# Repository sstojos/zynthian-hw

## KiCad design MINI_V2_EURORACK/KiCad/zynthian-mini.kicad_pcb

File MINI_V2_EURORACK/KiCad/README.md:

This repo include design details for building PCB for Zynthian MINI V2 to fit inside the Eurorack case.

PCB is designed usign KiCad software. 

This repository also include PCB that is used as a facia.

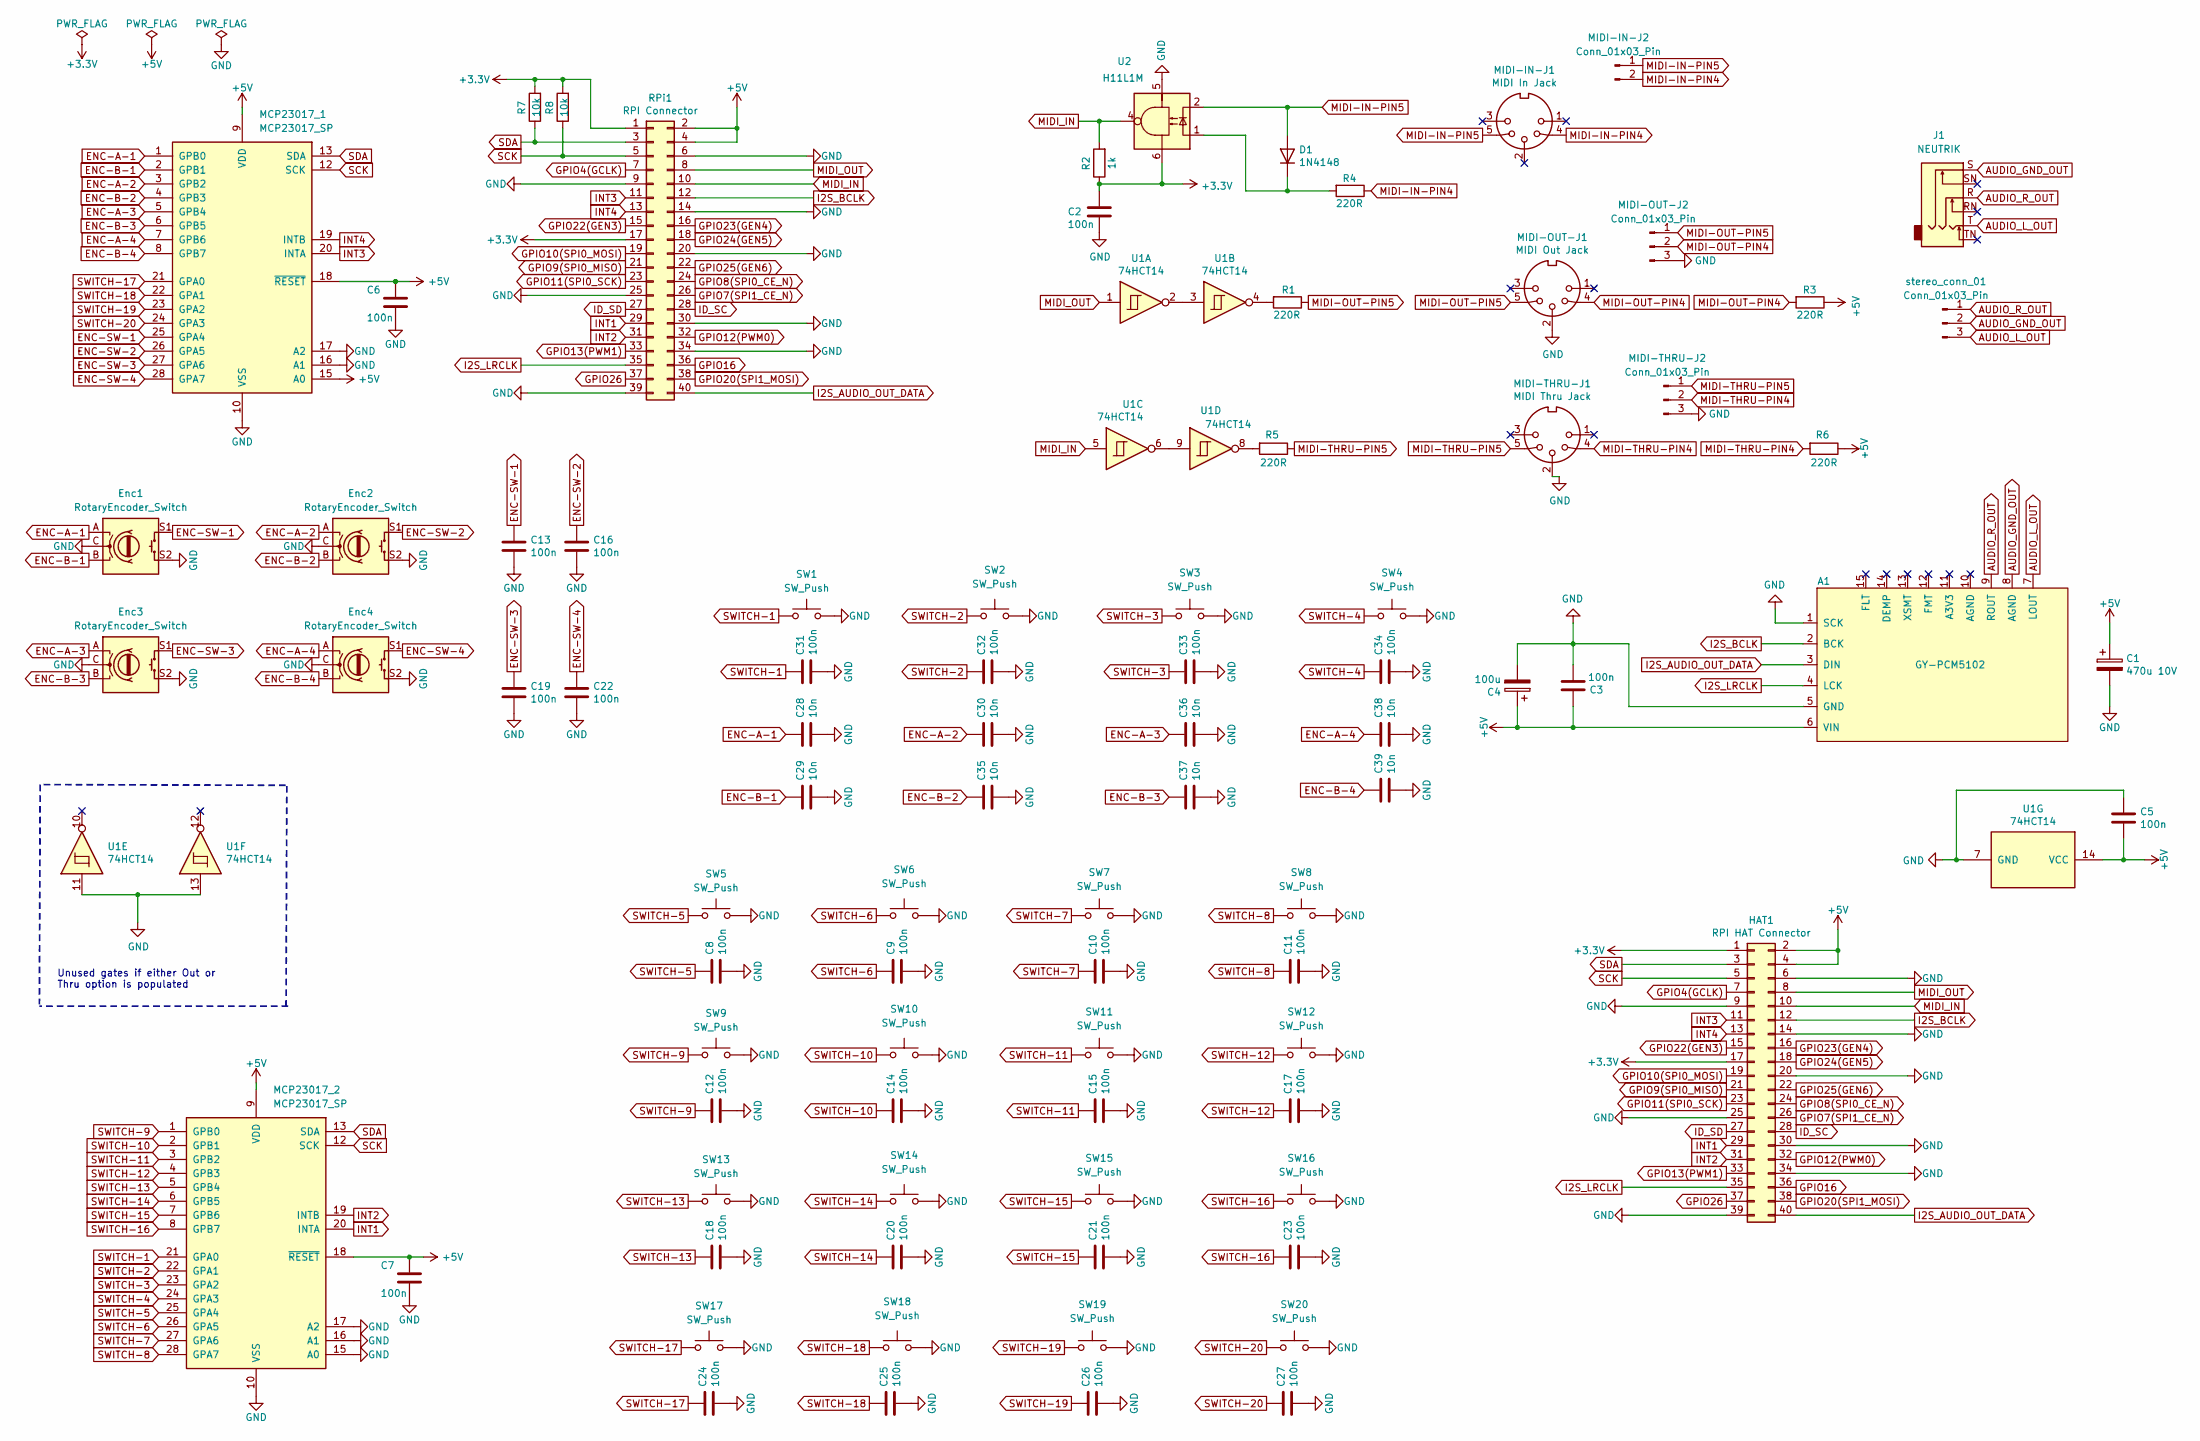
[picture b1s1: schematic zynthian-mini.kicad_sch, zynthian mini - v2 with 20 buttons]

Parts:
A1: GY-PCM5102
C1: 470u 10V; CP_Radial_D8.0mm_P3.50mm
C2, C3, C5, C6, C7: 100n; C_Rect_L7.0mm_W2.0mm_P5.00mm
C4: 100u; CP_Radial_D6.3mm_P2.50mm
C8, C9, C10, C11, C12, C13, C14, C15, C16, C17, C18, C19, C20, C21, C22, C23, C24, C25, C26, C27, C31, C32, C33, C34: 100n; C_Rect_L4.0mm_W2.5mm_P2.50mm
C28, C29, C30, C35, C36, C37, C38, C39: 10n; C_Rect_L4.0mm_W2.5mm_P2.50mm
D1: 1N4148; D_DO-35_SOD27_P7.62mm_Horizontal
Enc1, Enc2, Enc3, Enc4: RotaryEncoder_Switch; RotaryEncoder_Alps_EC12E-Switch_Vertical_H20mm
HAT1: RPI HAT Connector; raspberry pi 4
J1: NEUTRIK; Jack_6.35mm_Neutrik_NMJ6HFD2_Horizontal
MCP23017_1, MCP23017_2: MCP23017_SP; DIP-28_W7.62mm
MIDI-IN-J1: MIDI In Jack; MultiDIN5
MIDI-IN-J2: Conn_01x03_Pin; PinHeader_1x02_P2.54mm_Vertical
MIDI-OUT-J1: MIDI Out Jack; MultiDIN5
MIDI-OUT-J2: Conn_01x03_Pin; PinHeader_1x03_P2.54mm_Vertical
MIDI-THRU-J1: MIDI Thru Jack; MultiDIN5
MIDI-THRU-J2: Conn_01x03_Pin; PinHeader_1x03_P2.54mm_Vertical
R1, R3, R4, R5, R6: 220R; R_Axial_DIN0207_L6.3mm_D2.5mm_P7.62mm_Horizontal
R2: 1k; R_Axial_DIN0207_L6.3mm_D2.5mm_P7.62mm_Horizontal
R7, R8: 10k; R_Axial_DIN0207_L6.3mm_D2.5mm_P7.62mm_Horizontal
RPi1: RPI Connector; raspberry pi 4 HAT
SW1, SW2, SW3, SW4, SW5, SW6, SW7, SW8, SW9, SW10, SW11, SW12, SW13, SW14, SW15, SW16, SW17, SW18, SW19, SW20: SW_Push; push-button-13mm
U1: 74HCT14; DIP-14_W7.62mm
U2: H11L1M; DIP-6_W7.62mm
stereo_conn_01: Conn_01x03_Pin; PinHeader_1x03_P2.54mm_Vertical

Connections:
AUDIO_GND_OUT: A1.8 (AGND), J1.S, stereo_conn_01.2
AUDIO_L_OUT: A1.7 (LOUT), J1.T, stereo_conn_01.3
AUDIO_R_OUT: A1.9 (ROUT), J1.R, stereo_conn_01.1
ENC-A-1: C28.1, Enc1.A, MCP23017_1.1 (GPB0)
ENC-A-2: C30.1, Enc2.A, MCP23017_1.3 (GPB2)
ENC-A-3: C36.1, Enc3.A, MCP23017_1.5 (GPB4)
ENC-A-4: C38.1, Enc4.A, MCP23017_1.7 (GPB6)
ENC-B-1: C29.1, Enc1.B, MCP23017_1.2 (GPB1)
ENC-B-2: C35.1, Enc2.B, MCP23017_1.4 (GPB3)
ENC-B-3: C37.1, Enc3.B, MCP23017_1.6 (GPB5)
ENC-B-4: C39.1, Enc4.B, MCP23017_1.8 (GPB7)
ENC-SW-1: C13.1, Enc1.S1, MCP23017_1.25 (GPA4)
ENC-SW-2: C16.1, Enc2.S1, MCP23017_1.26 (GPA5)
ENC-SW-3: C19.1, Enc3.S1, MCP23017_1.27 (GPA6)
ENC-SW-4: C22.1, Enc4.S1, MCP23017_1.28 (GPA7)
GPIO4(GCLK): HAT1.7, RPi1.7
GPIO7(SPI1_CE_N): HAT1.26, RPi1.26
GPIO8(SPI0_CE_N): HAT1.24, RPi1.24
GPIO9(SPI0_MISO): HAT1.21, RPi1.21
GPIO10(SPI0_MOSI): HAT1.19, RPi1.19
GPIO11(SPI0_SCK): HAT1.23, RPi1.23
GPIO12(PWM0): HAT1.32, RPi1.32
GPIO13(PWM1): HAT1.33, RPi1.33
GPIO16: HAT1.36, RPi1.36
GPIO20(SPI1_MOSI): HAT1.38, RPi1.38
GPIO22(GEN3): HAT1.15, RPi1.15
GPIO23(GEN4): HAT1.16, RPi1.16
GPIO24(GEN5): HAT1.18, RPi1.18
GPIO25(GEN6): HAT1.22, RPi1.22
GPIO26: HAT1.37, RPi1.37
I2S_AUDIO_OUT_DATA: A1.3 (DIN), HAT1.40, RPi1.40
I2S_BCLK: A1.2 (BCK), HAT1.12, RPi1.12
I2S_LRCLK: A1.4 (LCK), HAT1.35, RPi1.35
ID_SC: HAT1.28, RPi1.28
ID_SD: HAT1.27, RPi1.27
INT1: HAT1.29, MCP23017_2.20 (INTA), RPi1.29
INT2: HAT1.31, MCP23017_2.19 (INTB), RPi1.31
INT3: HAT1.11, MCP23017_1.20 (INTA), RPi1.11
INT4: HAT1.13, MCP23017_1.19 (INTB), RPi1.13
MIDI-IN-PIN4: MIDI-IN-J1.4, MIDI-IN-J2.2, R4.1
MIDI-IN-PIN5: D1.2 (A), MIDI-IN-J1.5, MIDI-IN-J2.1, U2.2
MIDI-OUT-PIN4: MIDI-OUT-J1.4, MIDI-OUT-J2.2, R3.2
MIDI-OUT-PIN5: MIDI-OUT-J1.5, MIDI-OUT-J2.1, R1.1
MIDI-THRU-PIN4: MIDI-THRU-J1.4, MIDI-THRU-J2.2, R6.2
MIDI-THRU-PIN5: MIDI-THRU-J1.5, MIDI-THRU-J2.1, R5.1
MIDI_IN: HAT1.10, R2.2, RPi1.10, U1.5, U2.4
MIDI_OUT: HAT1.8, RPi1.8, U1.1
unnamed: D1.1 (K), R4.2, U2.1
unnamed: R1.2, U1.4
unnamed: R5.2, U1.8
unnamed: U1.2, U1.3
unnamed: U1.6, U1.9
SCK: HAT1.5, MCP23017_1.12 (SCK), MCP23017_2.12 (SCK), R8.1, RPi1.5
SDA: HAT1.3, MCP23017_1.13 (SDA), MCP23017_2.13 (SDA), R7.1, RPi1.3
SWITCH-1: C31.1, MCP23017_2.21 (GPA0), SW1.1
SWITCH-2: C32.1, MCP23017_2.22 (GPA1), SW2.1
SWITCH-3: C33.1, MCP23017_2.23 (GPA2), SW3.1
SWITCH-4: C34.1, MCP23017_2.24 (GPA3), SW4.1
SWITCH-5: C8.1, MCP23017_2.25 (GPA4), SW5.1
SWITCH-6: C9.1, MCP23017_2.26 (GPA5), SW6.1
SWITCH-7: C10.1, MCP23017_2.27 (GPA6), SW7.1
SWITCH-8: C11.1, MCP23017_2.28 (GPA7), SW8.1
SWITCH-9: C12.1, MCP23017_2.1 (GPB0), SW9.1
SWITCH-10: C14.1, MCP23017_2.2 (GPB1), SW10.1
SWITCH-11: C15.1, MCP23017_2.3 (GPB2), SW11.1
SWITCH-12: C17.1, MCP23017_2.4 (GPB3), SW12.1
SWITCH-13: C18.1, MCP23017_2.5 (GPB4), SW13.1
SWITCH-14: C20.1, MCP23017_2.6 (GPB5), SW14.1
SWITCH-15: C21.1, MCP23017_2.7 (GPB6), SW15.1
SWITCH-16: C23.1, MCP23017_2.8 (GPB7), SW16.1
SWITCH-17: C24.1, MCP23017_1.21 (GPA0), SW17.1
SWITCH-18: C25.1, MCP23017_1.22 (GPA1), SW18.1
SWITCH-19: C26.1, MCP23017_1.23 (GPA2), SW19.1
SWITCH-20: C27.1, MCP23017_1.24 (GPA3), SW20.1

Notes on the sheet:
Unused gates if either Out or Thru option is populated

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
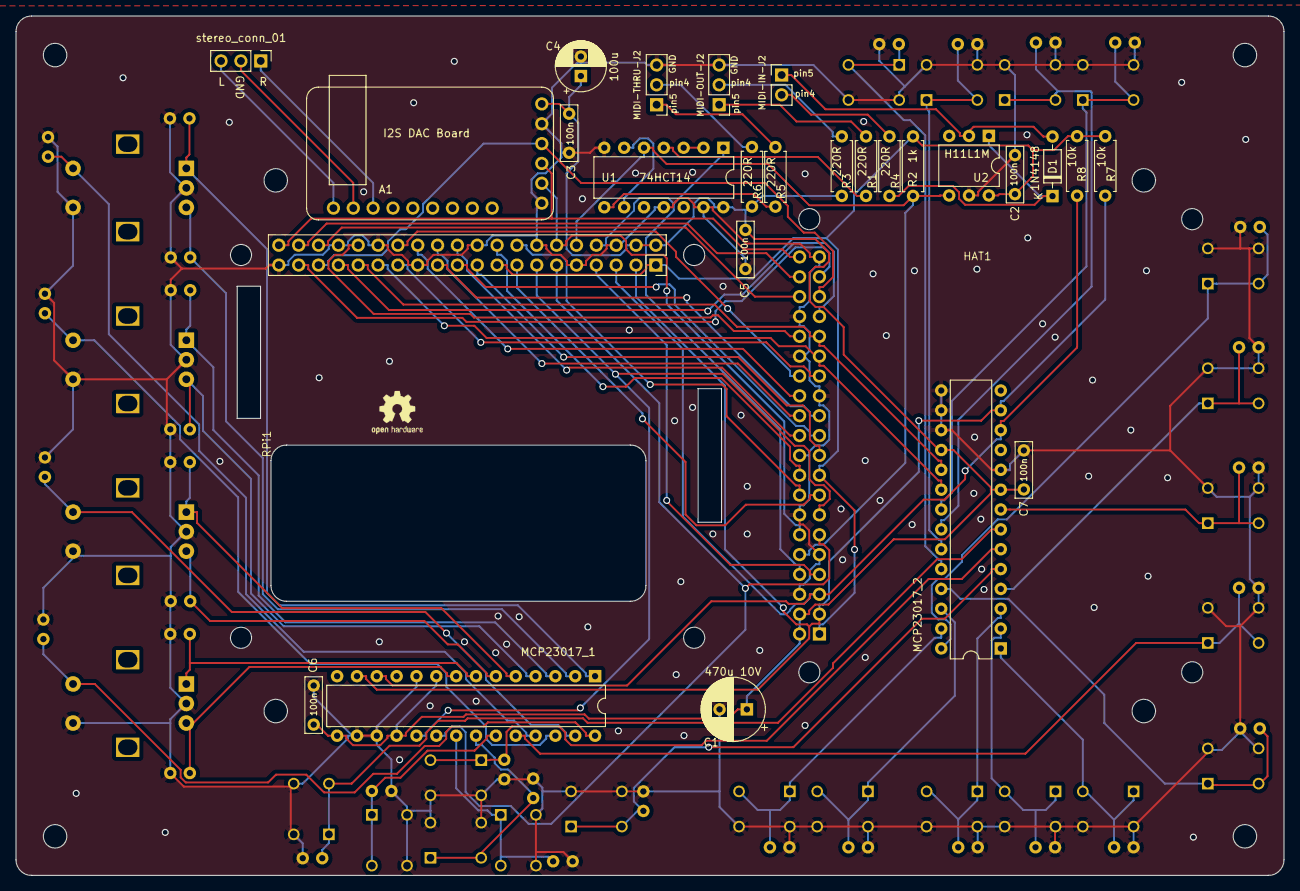
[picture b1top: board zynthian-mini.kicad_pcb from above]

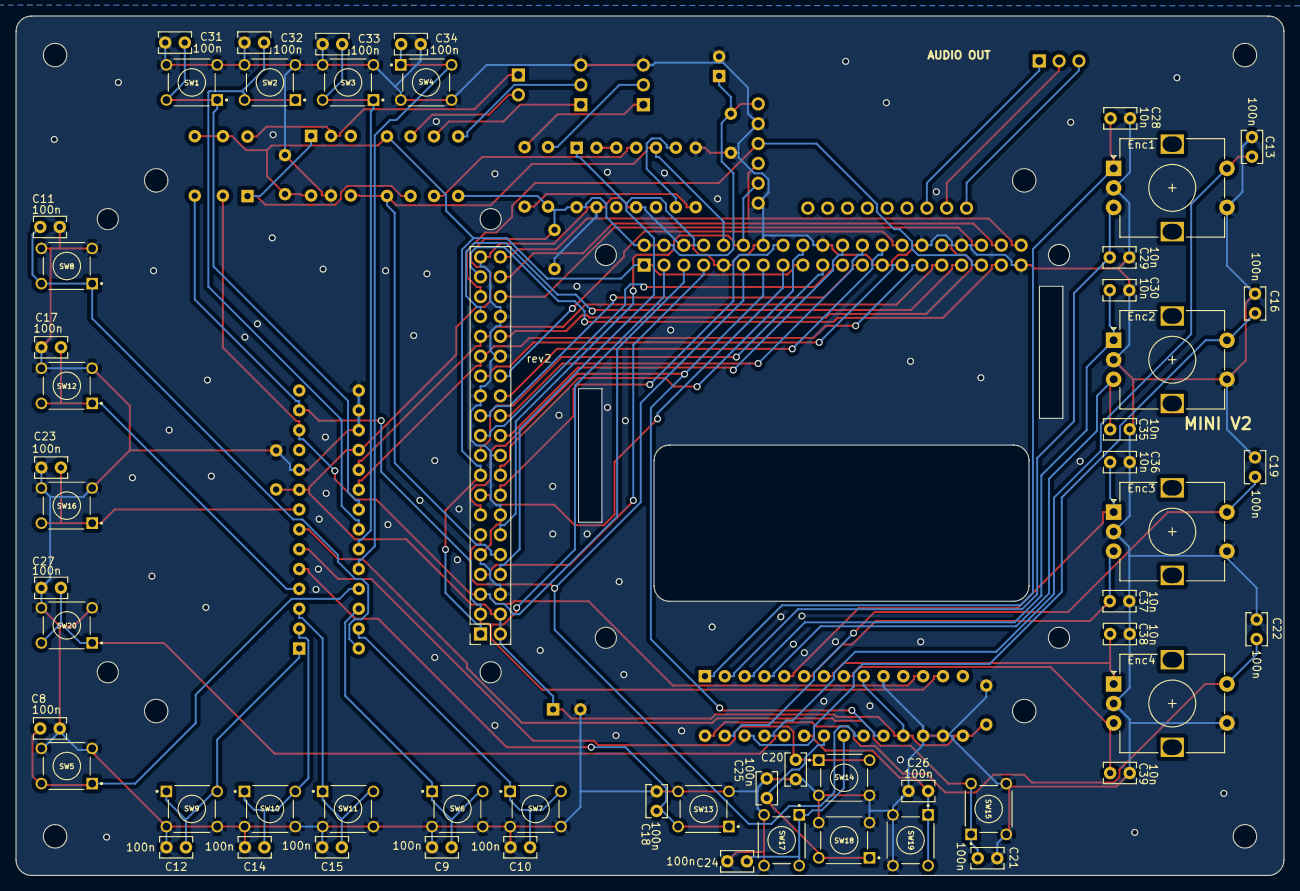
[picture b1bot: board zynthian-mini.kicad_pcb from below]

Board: 2 copper layers, 162.3 x 110.0 mm, 85 parts (57 on the bottom side), 77 nets.

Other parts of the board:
logo1: MINI V2; Zynthian Logo Mask
screen: aliexpress 5 inch screen

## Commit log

2024-10-24 added a first draft version
2024-10-24 updated to reflect that this is eurorack version
2024-10-24 removed some silkscreen printed references
